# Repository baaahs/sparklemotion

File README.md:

# Sparkle Motion

Sparkle Motion[^1] is the system used to control the lights on [BAAAHS](http://baaahs.org), but it's
designed so it could be applied to pretty much any lighting project. It includes a browser-based
light show designer and performance interface, 3D light mapping, IP-based control protocol, and
custom LED control hardware and firmware. We designed it all pretty much from scratch, because
we're nerds. We hope you'll have some fun with it and maybe find it useful.
[^1]: It's a [Donnie Darko](https://www.youtube.com/watch?v=4QJCn04dfek) [reference](https://wakeupdonnie.fandom.com/wiki/Sparkle_Motion).

|  |  |
| --- | --- |
| The Sparkle Motion [Simulator](https://baaahs.github.io/sparklemotion) | BAAAHS at Black Rock City, 2019 |

**tl;dr:**

Shows are built out of small scripts called shaders, which are written in
[GLSL](https://www.khronos.org/opengl/wiki/Core_Language_(GLSL)). Lots of [awesome](http://glslsandbox.com/)
[free](https://www.shadertoy.com/) shaders and [dev](https://github.com/radixzz/awesome-glsl)
[tools](https://shaderfrog.com/) already exist on the internet. In the show designer, you can create or
import shaders, and attach them to buttons or sliders in a customizable performance UI. Shaders can be
combined in interesting ways to create new effects. You can make shows reactive to the environment by
connecting external sensor data—like a beat detector, midi controller, sound spectral analysis, or a
webcam—to shader variables.

Sparkle Motion can control LED strips using industry-standard
[sACN](https://artisticlicenceintegration.com/technology-brief/technology-resource/sacn-and-art-net/)
(or with our custom IP protocol), and Sharpy-style moving heads
over DMX, but it could be extended to control pretty much any kind of device. Lights can be mapped to a
3D model using computer vision. Individual lighting fixtures, or groups of fixtures, can be controlled
separately. All types of lights are controlled using the same language and idioms.

On the hardware side, Sparkle Motion includes specs for an ESP32-based controller which you could build
(or [buy from us](mailto:info@baaahs.org)!) managing WS2812-family LEDs, which is controlled over
Ethernet or WiFi.

----

## Show Designer

A _show_ is a collection of shaders, attached to UI elements, which can be arbitrarily combined and made reactive to the
environment using sensors,

(more TK)

## Scene Configuration

Sparkle Motion shows may be designed with a specific model and display fixtures in mind, but most shows can be applied to any model and fixtures.

To facilitate this, Sparkle Motion separates configuration of scene elements (the physical model and fixtures) from visuals and the performance interface.

| Term | Definition |
| --- | --- |
| **Driver** | A pluggable software component that can talk to specific types of display controller hardware, e.g. Brains, WLED, or DMX USB dongles. |
| **Controller** | A physical component directly connected to display hardware, e.g. a Sparkle Motion Brain, a WLED controller, or a DMX USB dongle. One or more fixtures may be associated with a controller. |
| **Fixture** | A physical display device, e.g. a moving head, a pixel array surface (a.k.a. panel), an LED bar, etc. |
| **Scene/Stage?** | The collection of fixtures under control of Sparkle Motion, which may be identified as model entities, or anonymous. |
| **Geometry** | The physical shape of a pixel array fixture. |
| **Model** | A 3-dimensional model to which fixtures may be mapped. Models may be composed of OBJ files and explicitly placed entities. |
| **Entity** | An object within the model, e.g. a sheep panel or eye. |

Note that in some cases a single controller may control multiple fixtures. Commonly, a physical DMX USB dongle may have
multiple moving heads attached. It's possible (but less common) for a single brain or WLED controller to be attached to
multiple physical lighting fixtures.

Also, it's possible for a DMX controller to manage multiple DMX universes, e.g. in the case of a WLED controller
managing more than 170 pixels.

ERD:

Driver <->* Controller <->* Fixture <->? Entity *<--> Model

A fixture may be *identified* or *anomnymous*.

Identified fixtures are associated with an entity in the model, and therefore have a known position and geometry.

Anonymous fixtures are mostly for stuff like bikers-by. They are randomly placed within the model. Pixel arrays are assumed to be linear.

## Mapper

Sparkle Motion's mapper lets you detect arbitrarily-placed lights on a 2D or 3D model using just a camera
connected to a laptop.

(more TK)

## Hardware

(more TK)

[More here](brain/sw/README.md).

## Simulator

The entire system can be run within a web browser in simulation mode ([here!](https://baaahs.github.io/sparklemotion)). Every component is modeled in software
so you can see how it will behave in the real world.

-->

## Very Old Documentation
* [Show API](show_api.md) (outdated)
* [API docs](https://baaahs.github.io/sparklemotion/doc/sparklemotion/) (outdated)

## Prerequisites

1. Install [Java](https://www.oracle.com/java/technologies/javase-jdk11-downloads.html)
    - If using an arm64 mac, DMX device support for the native build of sparklemotion requires an x86 jdk which can be
      downloaded [here](https://jdk.java.net/archive/).
    - Make sure to pick a JDK < version 20 as [gradle does not currently
      support
it](https://youtrack.jetbrains.com/issue/KT-57669/Add-Java-20-to-JvmTarget).
1. Open as a gradle project with [IntelliJ](https://www.jetbrains.com/idea/download/)

## Running from source

### Simulator Mode

In simulator mode, most of Sparkle Motion runs within a web browser.

Run this in a shell window; a browser window will open with the simulator:

    ./gradlew --continuous jsBrowserDevelopmentRun

### Production Mode

In production mode, Sparkle Motion runs in a JVM process and talks to real hardware.

To start it, run:

    ./gradlew run

If you don't have a Brain running locally, do this too:

    ./gradlew runBrainJvm
    
When running in this mode you should be able to access the UI at http://localhost:8004 

### Builds the production (minified) js package

To build the production minified js package run:

```
./gradlew jsBrowserWebpack
```

## CI & Deployment

Continuous build here: https://circleci.com/gh/baaahs/sparklemotion

Passing builds are automatically deployed here: https://baaahs.github.io/sparklemotion

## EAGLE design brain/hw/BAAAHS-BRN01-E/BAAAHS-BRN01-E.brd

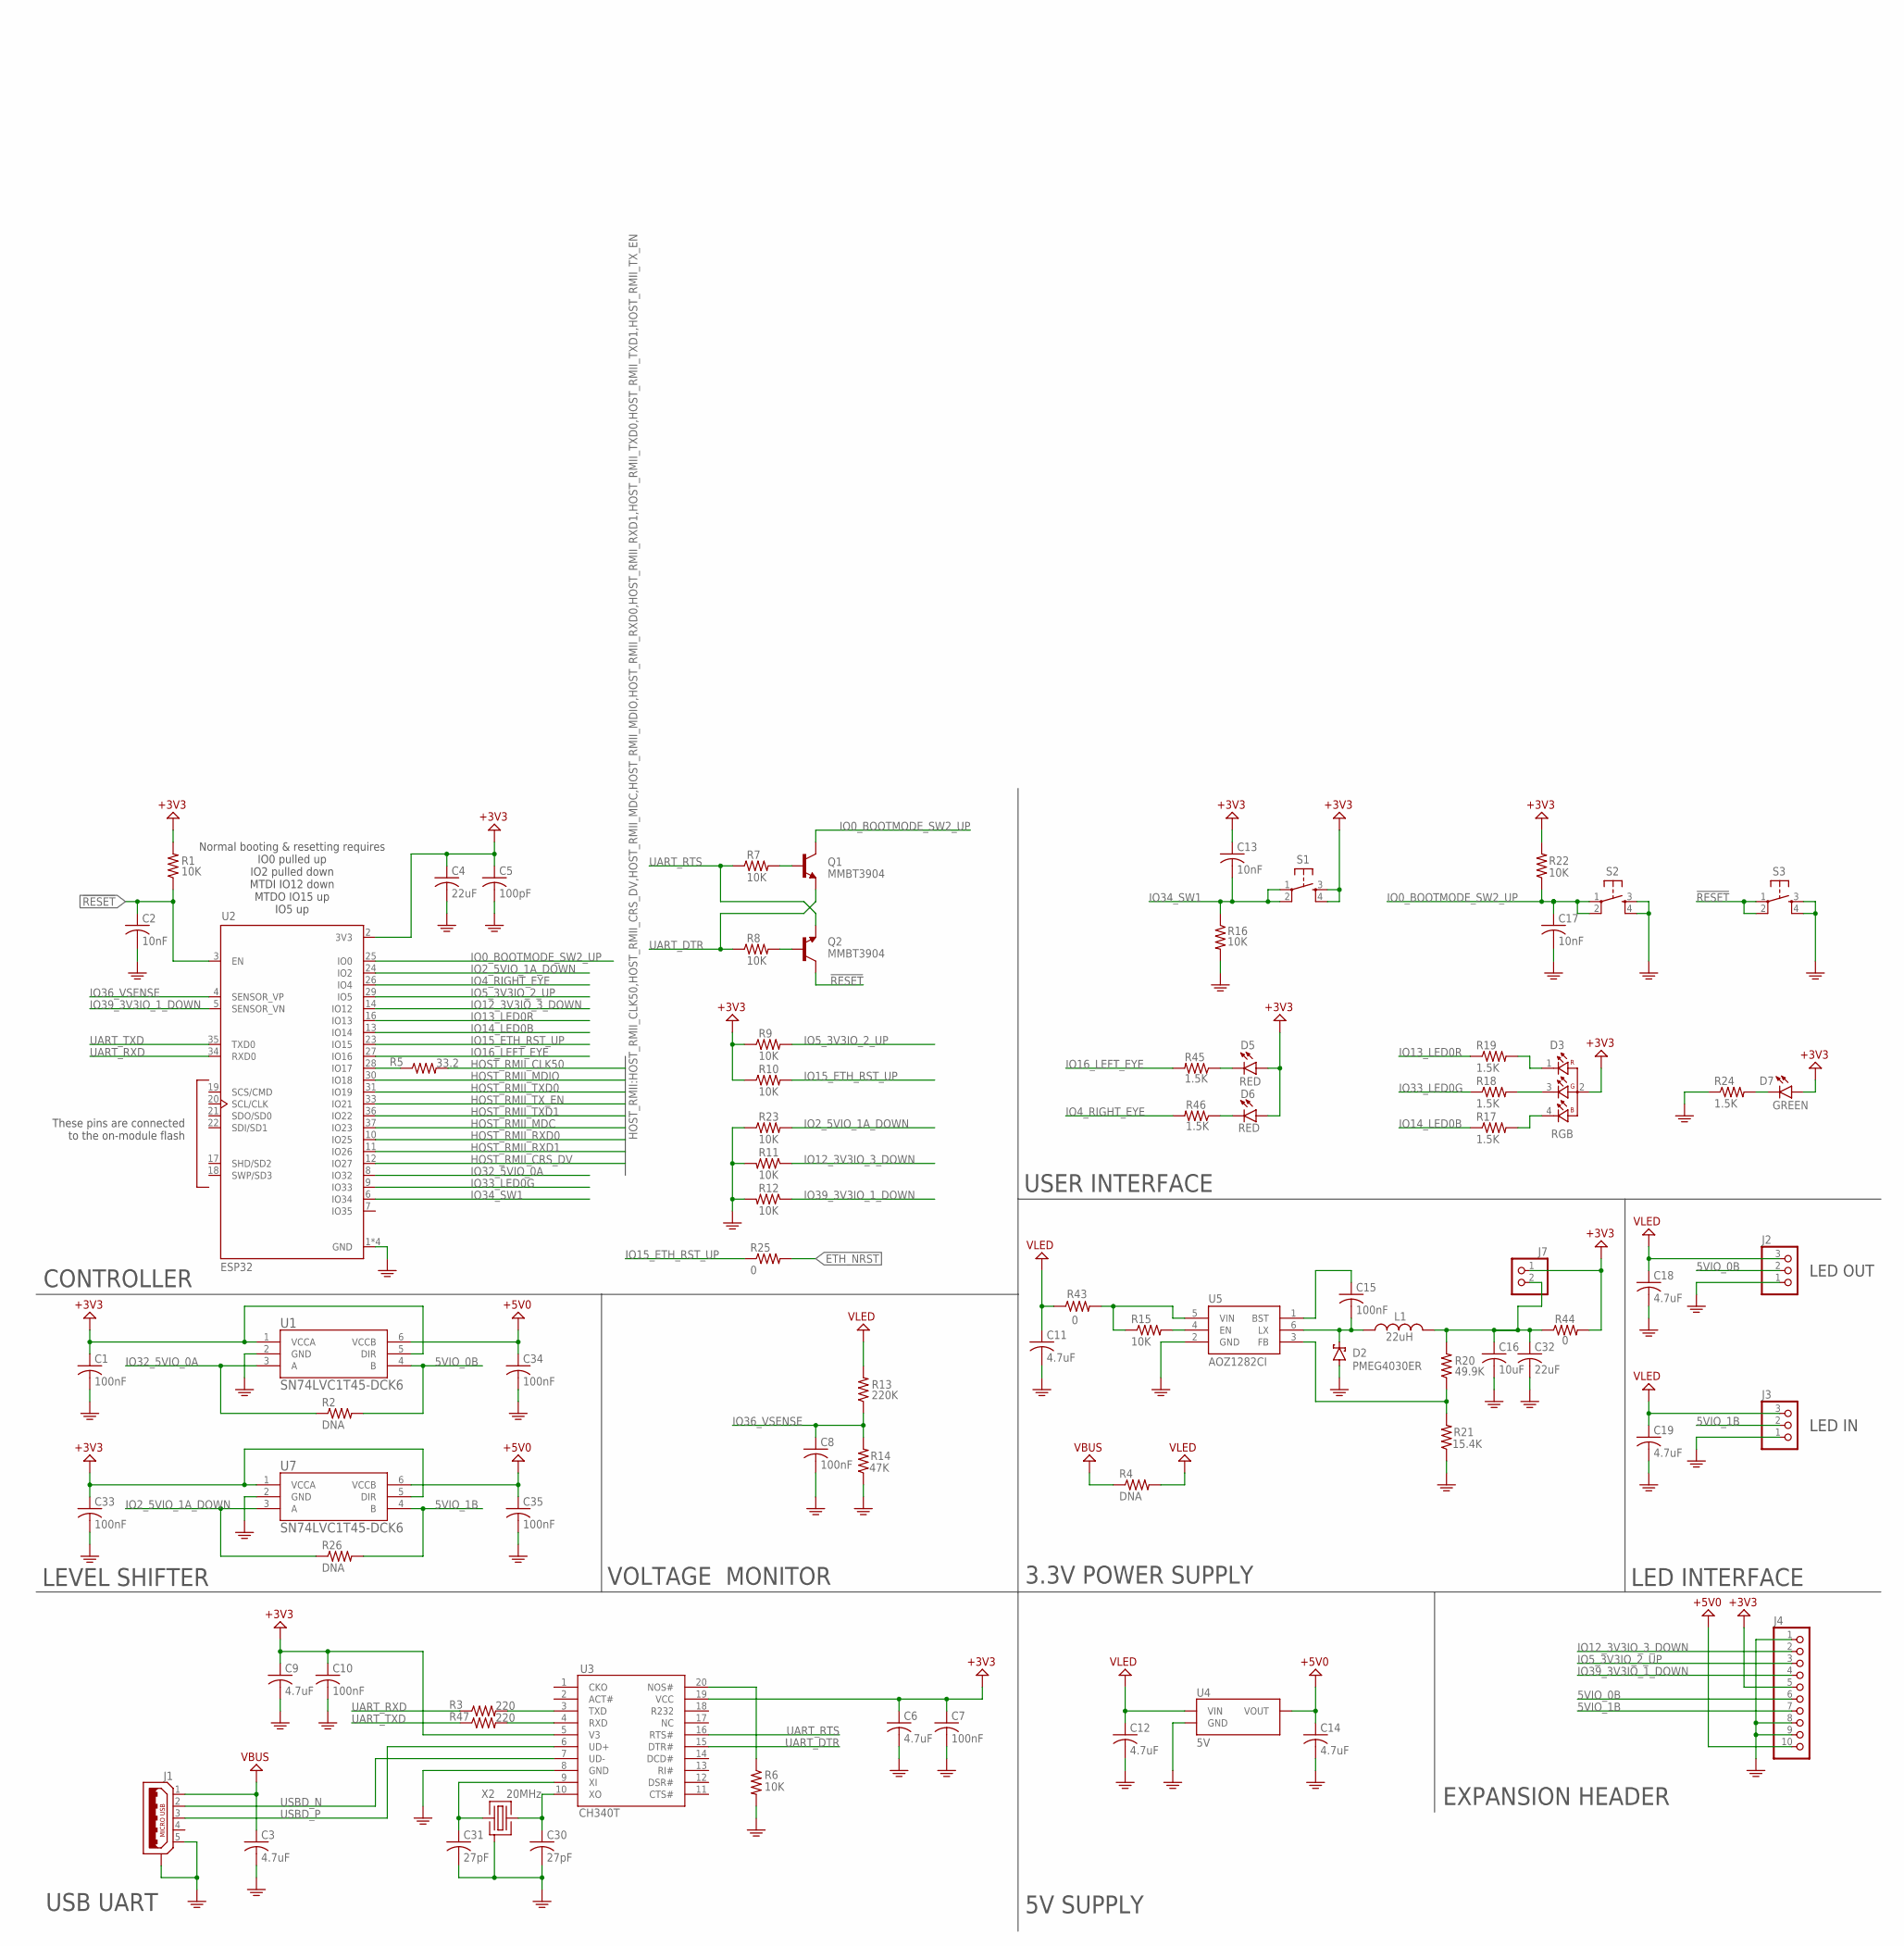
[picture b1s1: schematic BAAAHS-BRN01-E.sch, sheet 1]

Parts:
C1, C7, C8, C10, C15, C33, C34, C35: 100nF; C0402
C2, C13, C17: 10nF; C0402
C3, C6, C9, C14: 4.7uF; C0402
C4, C32: 22uF; C0603
C5: 100pF; C0402
C11, C12, C18, C19: 4.7uF; C0603
C16: 10uF; C0603
C30, C31: 27pF; C0402
D2: PMEG4030ER; SOD123
D3: RGB; RGB1616
D5, D6: RED; D0603
D7: GREEN; D0603
J1: USB_MICRO-FCI-USB_MICRO_A_RA; USB_MICRO_A_RA
J2, J3: PINHD1X3-20AWG; 3WAY_LED_WIRES
J4: PINHD1X10-1X10; 1X10
J7: PINHD1X2-1X02; 1X02
L1: 22uH; NRG4026
Q1, Q2: MMBT3904; SOT23
R1, R6, R7, R8, R9, R10, R11, R12, R15, R16, R22, R23: 10K; R0402
R2, R26: DNA; R0402
R3, R47: 220; R0402
R4: DNA; R0603
R5: 33.2; R0402
R13: 220K; R0402
R14: 47K; R0402
R17, R18, R19, R24, R45, R46: 1.5K; R0402
R20: 49.9K; R0402
R21: 15.4K; R0402
R25: 0; R0402
R43, R44: 0; R0603
S1, S2, S3: SW4-SM6MM; SM6MM
U1, U7: SN74LVC1T45-DCK6; DCK6
U2: ESP32; MODULE_ESP32WROOM32D
U3: CH340T; SSOP20
U4: 5V; SOT23
U5: AOZ1282CI; SOT23_6
X2: 20MHz; 3.2X2.5_4P

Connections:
3V3: C1.1, C4.1, C5.1, C6.1, C7.1, C9.1, C10.1, C13.1, C33.1, D3.2 (CA), D5.A, D6.A, D7.A, J4.5, J7.1, R1.2, R9.1, R10.1, R22.2, R44.2, S1.3 (S), S1.4 (S1), U1.1 (VCCA), U1.5 (DIR), U2.2 (3V3), U3.5 (V3), U3.19 (VCC), U7.1 (VCCA), U7.5 (DIR); also elsewhere on the board
5V0: C14.1, C34.1, C35.1, J4.10, U1.6 (VCCB), U4.2 (VOUT), U7.6 (VCCB)
5VIO_0B: J2.2, J4.6, R2.2, U1.4 (B)
5VIO_1B: J3.2, J4.7, R26.2, U7.4 (B)
!RESET: C2.1, Q2.3 (C), R1.1, S3.1, S3.2 (P1), U2.3 (EN)
ETH_NRST: R25.2; also elsewhere on the board
FB: R20.1, R21.2, U5.3 (FB)
GND: C1.2, C2.2, C3.2, C4.2, C5.2, C6.2, C7.2, C8.2, C9.2, C10.2, C11.2, C12.2, C14.2, C16.2, C17.2, C18.2, C19.2, C30.2, C31.2, C32.2, C33.2, C34.2, C35.2, D2.A, J1.5, J1.S1, J1.S2 (S1), J1.S3 (S1), J1.S4 (S1), J1.S5 (S1), J1.S6 (S1), J2.1 (3), J3.1 (3), J4.1, J4.8, J4.9, R6.2, R11.2, R12.2, R14.1, R16.2, R21.1, R23.1, R24.1, S2.3 (S), S2.4 (S1), S3.3 (S), S3.4 (S1), U1.2 (GND), U2.1 (GND), U2.15 (GND), U2.38 (GND), U2.39 (GND), U3.8 (GND), U4.1 (GND), U5.2 (GND), U7.2 (GND), X2.2 (SH), X2.4 (SH); also elsewhere on the board
HOST_RMII_CLK50: R5.2; also elsewhere on the board
HOST_RMII_CRS_DV: U2.12 (IO27); also elsewhere on the board
HOST_RMII_MDC: U2.37 (IO23); also elsewhere on the board
HOST_RMII_MDIO: U2.30 (IO18); also elsewhere on the board
HOST_RMII_RXD0: U2.10 (IO25); also elsewhere on the board
HOST_RMII_RXD1: U2.11 (IO26); also elsewhere on the board
HOST_RMII_TXD0: U2.31 (IO19); also elsewhere on the board
HOST_RMII_TXD1: U2.36 (IO22); also elsewhere on the board
HOST_RMII_TX_EN: U2.33 (IO21); also elsewhere on the board
IO0_BOOTMODE_SW2_UP: C17.1, Q1.3 (C), R22.1, S2.1, S2.2 (P1), U2.25 (IO0)
IO2_5VIO_1A_DOWN: R23.2, R26.1, U2.24 (IO2), U7.3 (A)
IO4_RIGHT_EYE: R46.2, U2.26 (IO4)
IO5_3V3IO_2_UP: J4.3, R9.2, U2.29 (IO5)
IO12_3V3IO_3_DOWN: J4.2, R11.1, U2.14 (IO12)
IO13_LED0R: R19.1, U2.16 (IO13)
IO14_LED0B: R17.1, U2.13 (IO14)
IO15_ETH_RST_UP: R10.2, R25.1, U2.23 (IO15)
IO16_LEFT_EYE: R45.2, U2.27 (IO16)
IO32_5VIO_0A: R2.1, U1.3 (A), U2.8 (IO32)
IO33_LED0G: R18.1, U2.9 (IO33)
IO34_SW1: C13.2, R16.1, S1.1, S1.2 (P1), U2.6 (IO34)
IO36_VSENSE: C8.1, R13.1, R14.2, U2.4 (SENSOR_VP)
IO39_3V3IO_1_DOWN: J4.4, R12.1, U2.5 (SENSOR_VN)
unnamed: R5.1, U2.28 (IO17)
unnamed: R15.2, U5.4 (EN)
unnamed: C15.2, D2.C, L1.1, U5.6 (LX)
unnamed: R3.2, U3.3 (TXD)
unnamed: R47.2, U3.4 (RXD)
unnamed: Q2.1 (B), R8.2
unnamed: Q1.1 (B), R7.2
unnamed: D3.4 (B), R17.2
unnamed: D3.3 (G), R18.2
unnamed: D3.1 (R), R19.2
unnamed: C31.1, U3.9 (XI), X2.3 (2)
unnamed: C30.1, U3.10 (XO), X2.1
unnamed: D7.C, R24.2
unnamed: C15.1, U5.1 (BST)
unnamed: R15.1, R43.2, U5.5 (VIN)
unnamed: C16.1, C32.1, J7.2, L1.2, R20.2, R44.1
unnamed: D6.C, R46.1
unnamed: D5.C, R45.1
NOS#: R6.1, U3.20 (NOS#)
UART_DTR: Q1.2 (E), R8.1, U3.15 (DTR#)
UART_RTS: Q2.2 (E), R7.1, U3.16 (RTS#)
UART_RXD: R3.1, U2.34 (RXD0)
UART_TXD: R47.1, U2.35 (TXD0)
USBD_N: J1.2, U3.7 (UD-)
USBD_P: J1.3, U3.6 (UD+)
VBUS: C3.1, J1.1, R4.1
VLED: C11.1, C12.1, C18.1, C19.1, J2.3 (1), J3.3 (1), R4.2, R13.2, R43.1, U4.3 (VIN)

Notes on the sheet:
Normal booting & resetting requires IO0 pulled up IO2 pulled down MTDI IO12 down MTDO IO15 up IO5 up
These pins are connected to the on-module flash
CONTROLLER
LEVEL SHIFTER
USB UART
5V SUPPLY
3.3V POWER SUPPLY
EXPANSION HEADER
LED INTERFACE
USER INTERFACE
VOLTAGE MONITOR
LED OUT
LED IN

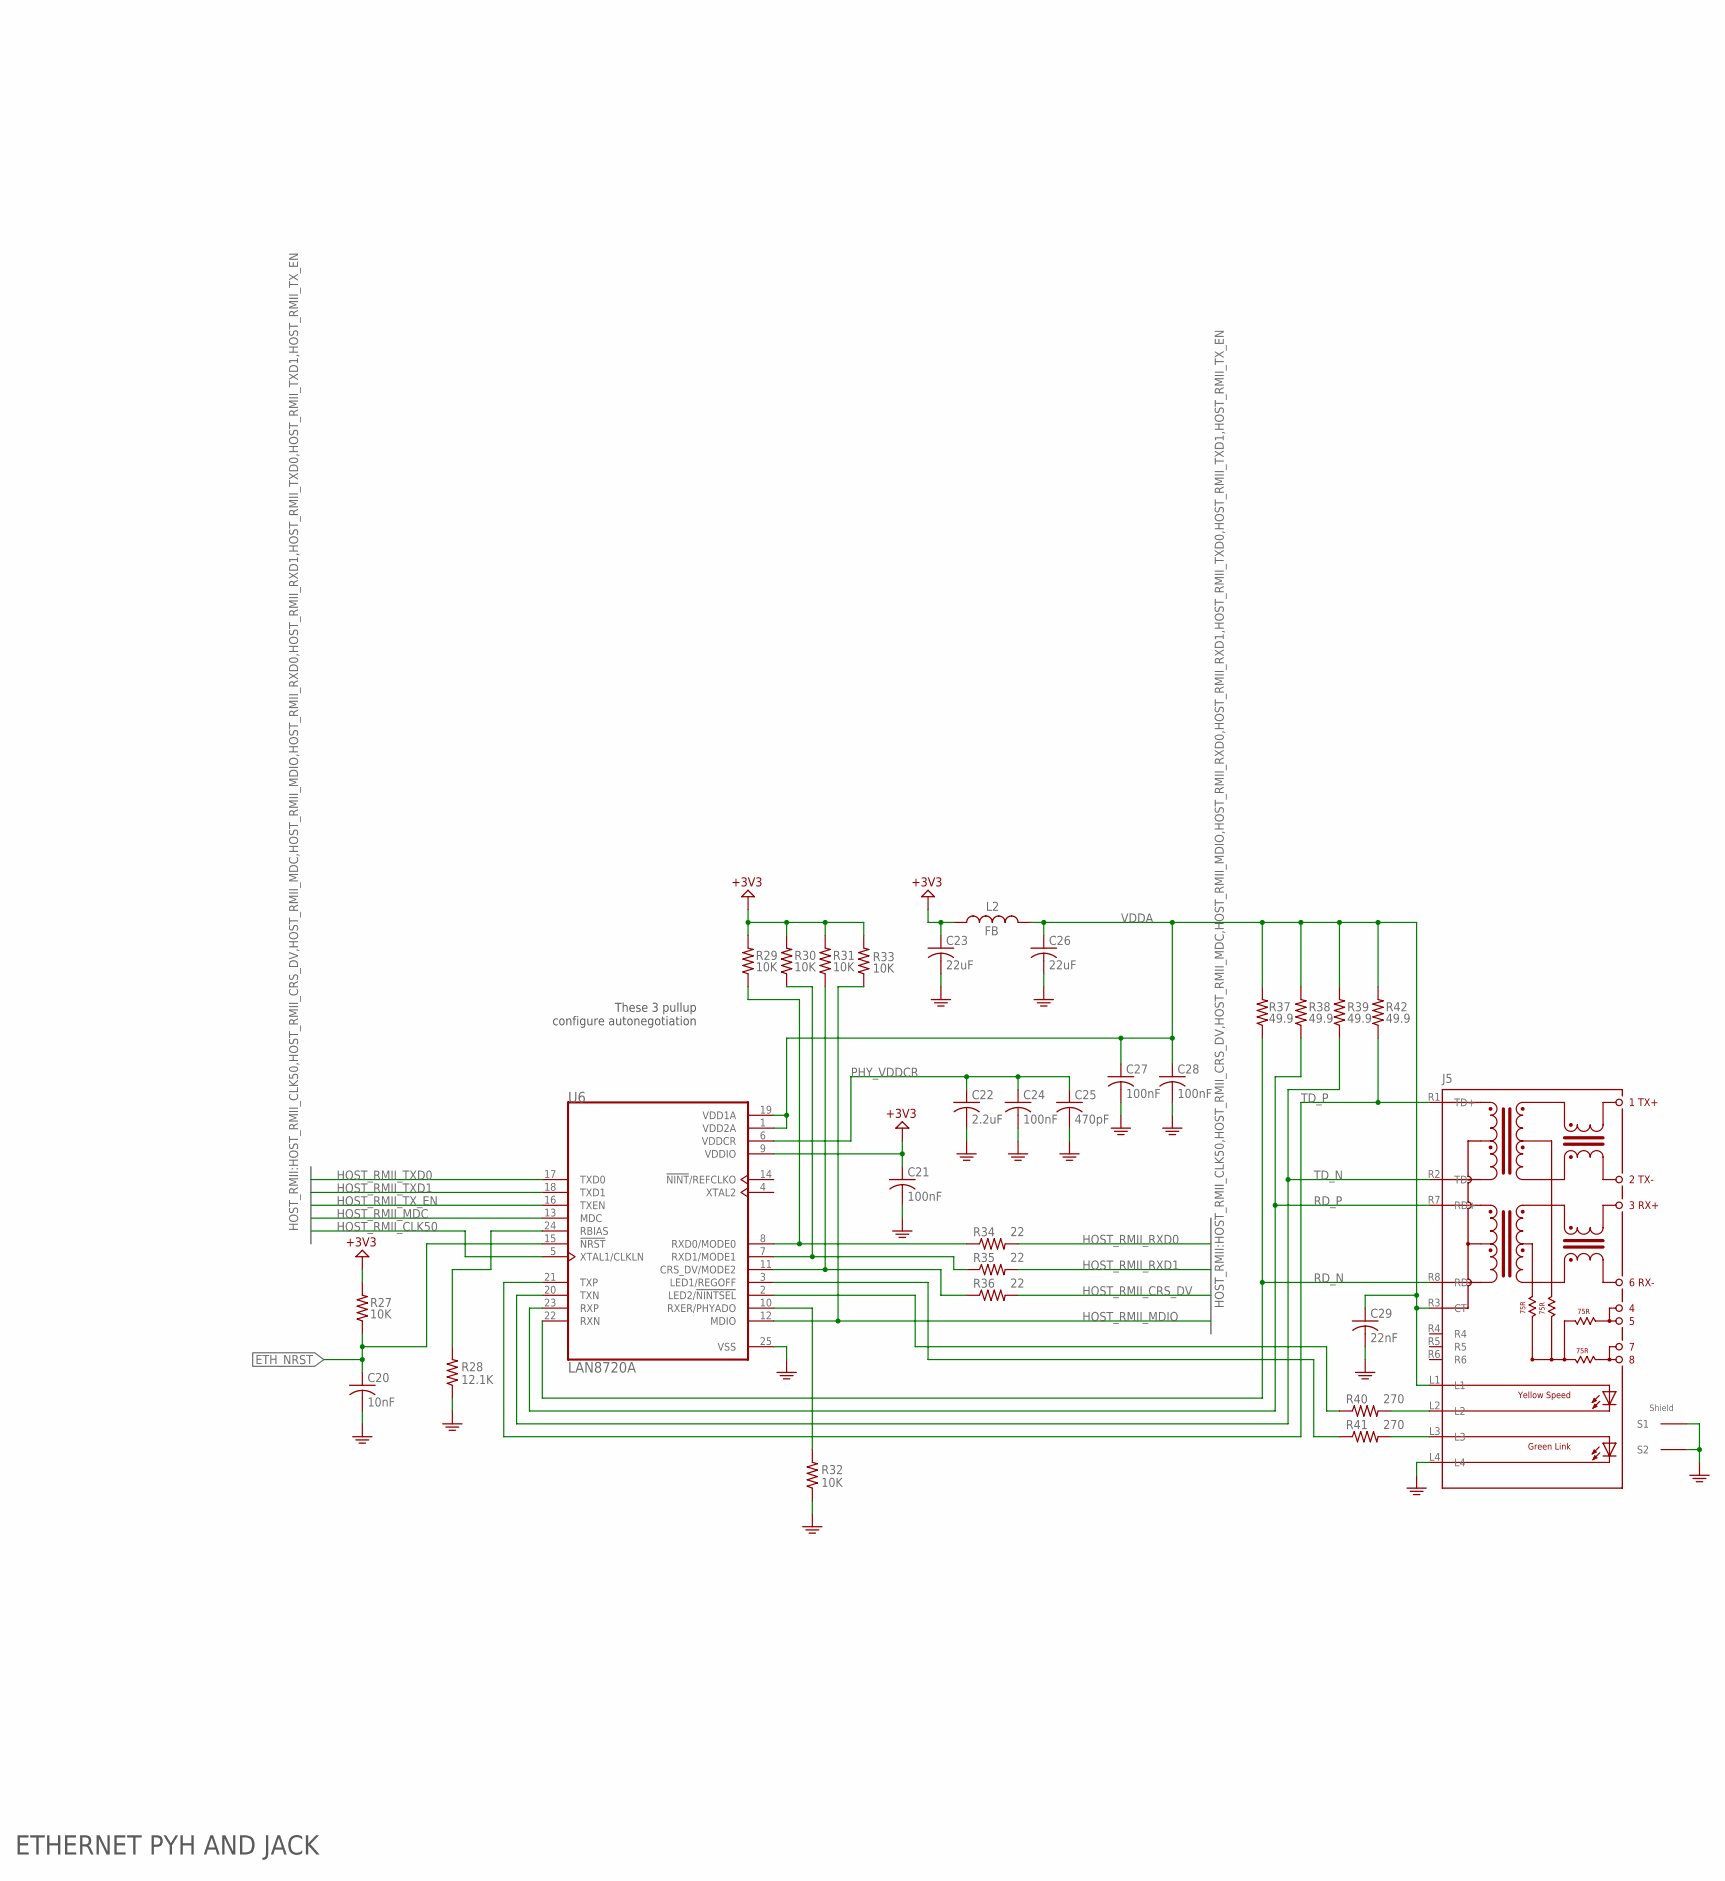
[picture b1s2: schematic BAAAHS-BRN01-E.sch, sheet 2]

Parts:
C20: 10nF; C0402
C21, C24, C27, C28: 100nF; C0402
C22: 2.2uF; C0603
C23, C26: 22uF; C0603
C25: 470pF; C0402
C29: 22nF; C0402
J5: RB1-125BAG1A; WIZNET_RB1-125BAG1A
L2: FB; L0603
R27, R29, R30, R31, R32, R33: 10K; R0402
R28: 12.1K; R0402
R34, R35, R36: 22; R0402
R37, R38, R39, R42: 49.9; R0402
R40, R41: 270; R0402
U6: LAN8720A; QFN50P400X400X100-25N

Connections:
3V3: C21.1, C23.1, L2.1, R27.2, R29.2, R30.2, R31.2, R33.2, U6.9 (VDDIO); also elsewhere on the board
ETH_NRST: C20.1, R27.1, U6.15 (!NRST); also elsewhere on the board
GND: C20.2, C21.2, C22.2, C23.2, C24.2, C25.2, C26.2, C27.2, C28.2, C29.2, J5.L4, J5.S1, J5.S2, R28.1, R32.1, U6.25 (VSS); also elsewhere on the board
HOST_RMII_CLK50: U6.5 (XTAL1/CLKLN); also elsewhere on the board
HOST_RMII_CRS_DV: R36.2; also elsewhere on the board
HOST_RMII_MDC: U6.13 (MDC); also elsewhere on the board
HOST_RMII_MDIO: R33.1, U6.12 (MDIO); also elsewhere on the board
HOST_RMII_RXD0: R34.2; also elsewhere on the board
HOST_RMII_RXD1: R35.2; also elsewhere on the board
HOST_RMII_TXD0: U6.17 (TXD0); also elsewhere on the board
HOST_RMII_TXD1: U6.18 (TXD1); also elsewhere on the board
HOST_RMII_TX_EN: U6.16 (TXEN); also elsewhere on the board
unnamed: J5.L3, R41.2
unnamed: R31.1, R36.1, U6.11 (CRS_DV/MODE2)
unnamed: R30.1, R35.1, U6.7 (RXD1/MODE1)
unnamed: R29.1, R34.1, U6.8 (RXD0/MODE0)
unnamed: R28.2, U6.24 (RBIAS)
unnamed: R41.1, U6.3 (LED1/REGOFF)
unnamed: R40.1, U6.2 (LED2/!NINTSEL!)
unnamed: J5.L2, R40.2
unnamed: R32.2, U6.10 (RXER/PHYADO)
PHY_VDDCR: C22.1, C24.1, C25.1, U6.6 (VDDCR)
RD_N: J5.R8 (RD-), R37.1, U6.22 (RXN)
RD_P: J5.R7 (RD+), R38.1, U6.23 (RXP)
TD_N: J5.R2 (TD-), R39.1, U6.20 (TXN)
TD_P: J5.R1 (TD+), R42.1, U6.21 (TXP)
VDDA: C26.1, C27.1, C28.1, C29.1, J5.L1, J5.R3 (CT), L2.2, R37.2, R38.2, R39.2, R42.2, U6.1 (VDD2A), U6.19 (VDD1A)

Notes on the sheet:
These 3 pullup configure autonegotiation
ETHERNET PYH AND JACK

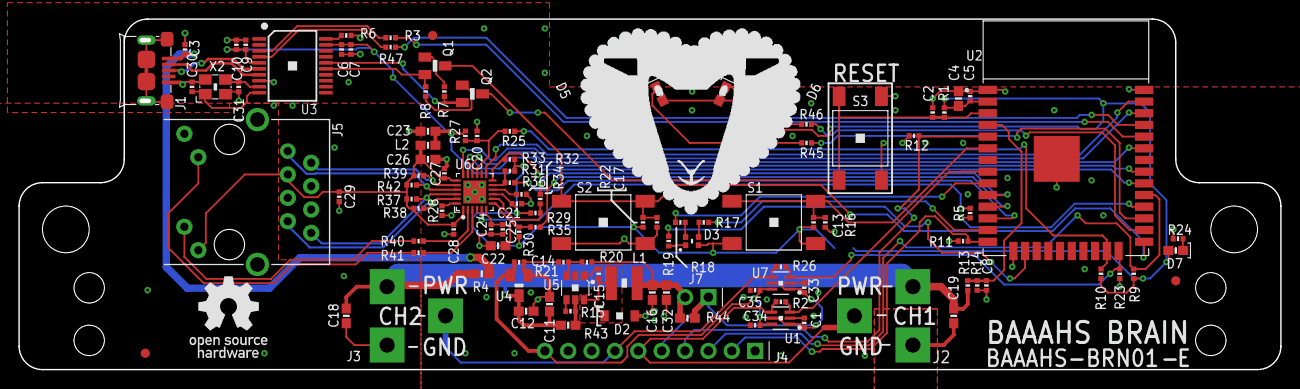
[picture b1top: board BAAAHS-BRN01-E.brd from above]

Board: 4 copper layers, 136.8 x 37.7 mm, 117 parts (1 on the bottom side), 73 nets.

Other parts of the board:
F1, F2, F3: FIDUCIAL_1MM
U$1: NOTE_ENIG_BLACK_NARROW
U$9: BAAAHS_FABRICATION_TITLEBLOCK
U$10: STACKUP_4LAYER_1.6MM
U$16: BAAAHS_TOP_ASSEMBLY_TITLEBLOCK
U$17: OPEN_HARDWARE_LOGO_350
U$18: BAAAHS_LOGO

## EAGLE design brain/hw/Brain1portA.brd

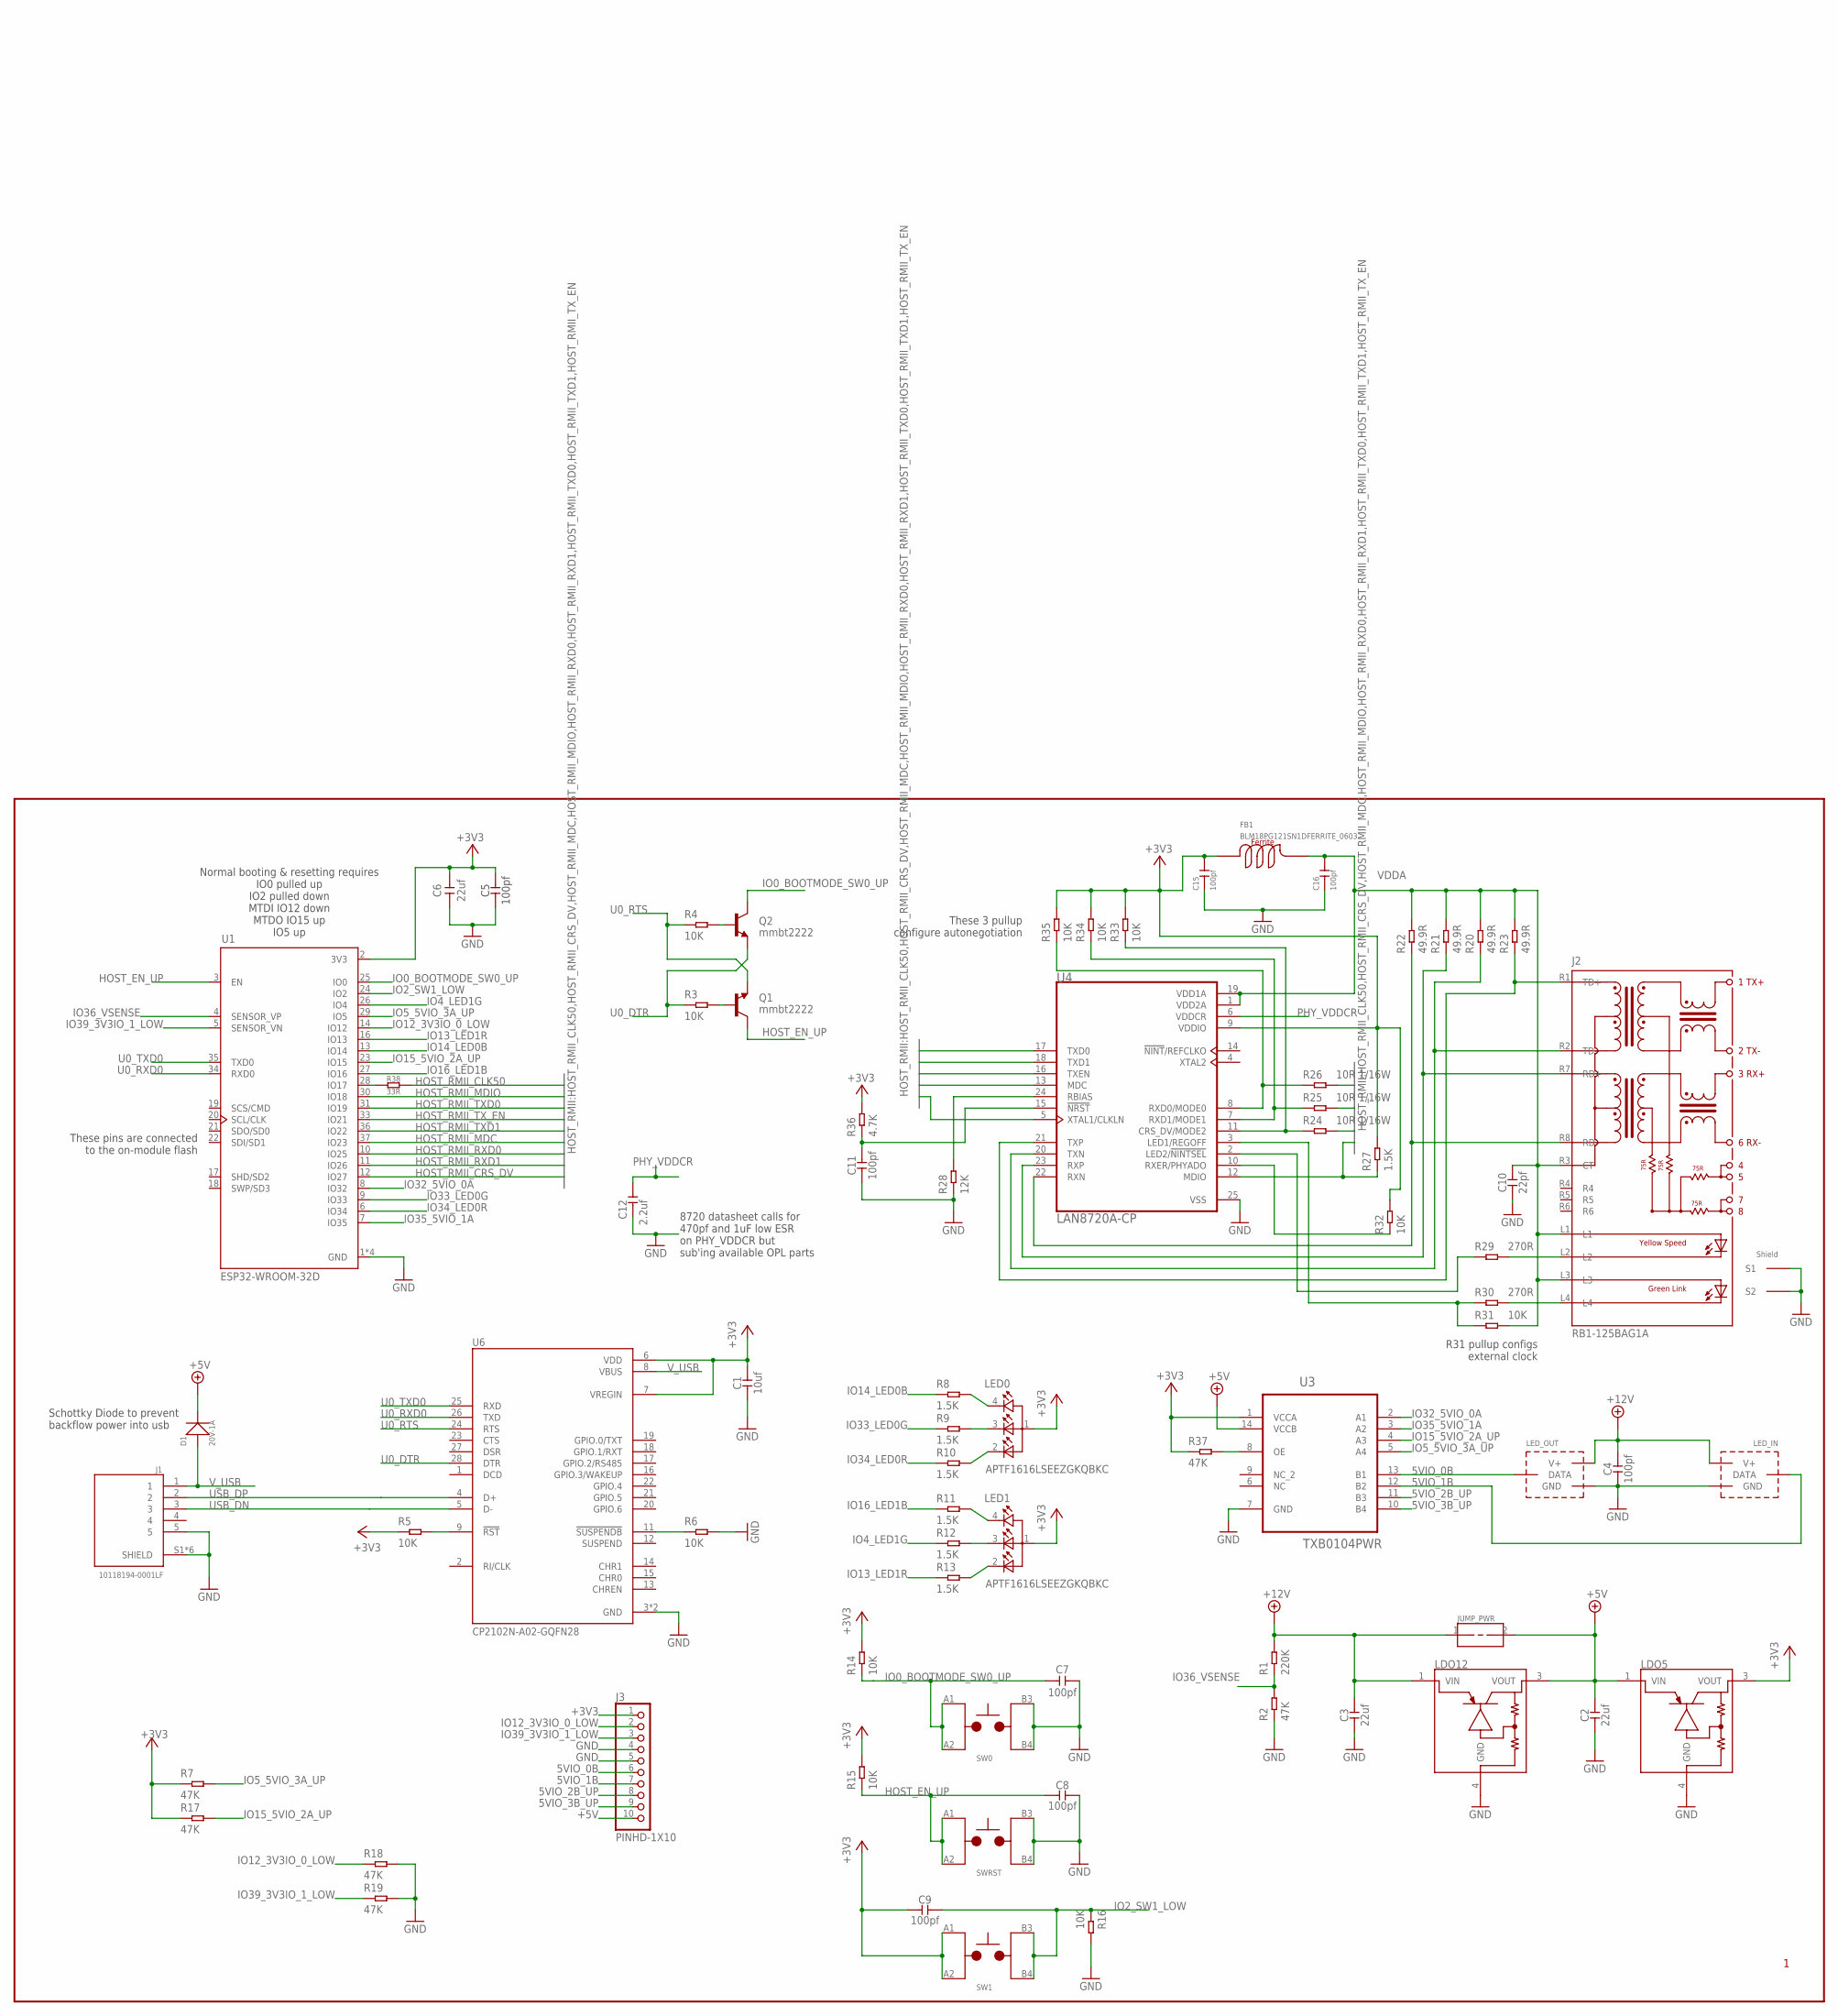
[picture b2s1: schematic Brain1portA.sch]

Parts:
C1: 10uf; C0402
C2, C3, C6: 22uf; C0805
C4, C5, C7, C8, C9, C11, C15, C16: 100pf; C0402
C10: 22pf; C0402
C12: 2.2uf; C0603
D1: 20V-1A; SOD-123
FB1: BLM18PG121SN1DFERRITE_0603; L0603
J1: 10118194-0001LF; AMPHENOL_10118194-0001LF
J2: RB1-125BAG1A; WIZNET_RB1-125BAG1A
J3: PINHD-1X10; 1X10-BIG
JUMP_PWR: PWR_SUPPLY_SHORT050_DRILLED; SHORT_050_DRILLED
LDO5, LDO12: NCP5501DPAK3; TO229P990X238-3
LED0, LED1: APTF1616LSEEZGKQBKC; LEDSC160X160X070-4N
LED_IN: 3WAY_LED_CONWIRES; 3WAY_LED_WIRES
LED_OUT: 3WAY_LED_CONWIRES; 3WAY_LED_WIRES
Q1, Q2: mmbt2222; SOT23-BEC
R1: 220K; R0402
R2, R7, R17, R18, R19, R37: 47K; R0402
R3, R4, R5, R6, R14, R15, R16, R31, R32, R33, R34, R35: 10K; R0402
R8, R9, R10, R11, R12, R13, R27: 1.5K; R0402
R20, R21, R22, R23: 49.9R; R0402
R24, R25, R26: 10R 1/16W; R0402
R28: 12K; R0402
R29, R30: 270R; R0402
R36: 4.7K; R0402
R38: 33R; R0603
SW0, SW1: TL3301T3301SWITCH; SW-4
SWRST: TL3301T3301SWITCH; SW-4
U1: ESP32-WROOM-32D; MODULE_ESP32-WROOM-32D
U3: TXB0104PWR; SOP65P640X120-14N
U4: LAN8720A-CP; QFN50P400X400X100-25N
U6: CP2102N-A02-GQFN28; QFN50P500X500X80-29N

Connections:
5VIO_0B: J3.6, LED_OUT.DATA, U3.13 (B1)
5VIO_1B: J3.7, LED_IN.DATA, U3.12 (B2)
5VIO_2B_UP: J3.8, U3.11 (B3)
5VIO_3B_UP: J3.9, U3.10 (B4)
+3V3: C1.1, C5.1, C6.1, C9.1, C15.2, FB1.1, J3.1, LDO5.3 (VOUT), LED0.1, LED1.1, R5.1, R7.1, R14.2, R15.2, R17.1, R27.2, R32.2, R33.2, R34.2, R35.2, R36.2, R37.1, SW1.A1 (1), SW1.A2 (2), U1.2 (3V3), U3.1 (VCCA), U4.9 (VDDIO), U6.6 (VDD), U6.7 (VREGIN)
+5V: C2.1, D1.-, J3.10, JUMP_PWR.2, LDO5.1 (VIN), LDO12.3 (VOUT), U3.14 (VCCB)
+12V: C3.1, C4.1, JUMP_PWR.1, LDO12.1 (VIN), LED_IN.V+, LED_OUT.V+, R1.2
GND: C1.2, C2.2, C3.2, C4.2, C5.2, C6.2, C7.2, C8.2, C10.2, C11.2, C12.2, C15.1, C16.1, J1.5, J1.S1 (SHIELD), J1.S2 (SHIELD), J1.S3 (SHIELD), J1.S4 (SHIELD), J1.S5 (SHIELD), J1.S6 (SHIELD), J2.S1, J2.S2, J3.4, J3.5, LDO5.4 (GND), LDO12.4 (GND), LED_IN.GND, LED_OUT.GND, R2.1, R6.2, R16.2, R18.2, R19.2, R28.1, SW0.B3 (3), SW0.B4 (4), SWRST.B3 (3), SWRST.B4 (4), U1.1 (GND), U1.15 (GND), U1.38 (GND), U1.39 (GND), U3.7 (GND), U4.25 (VSS), U6.3 (GND), U6.29 (GND)
HOST_EN_UP: C8.1, Q1.C, R15.1, SWRST.A1 (1), SWRST.A2 (2), U1.3 (EN)
HOST_RMII_CLK50: R38.2, U4.5 (XTAL1/CLKLN)
HOST_RMII_CRS_DV: R24.2, U1.12 (IO27)
HOST_RMII_MDC: U1.37 (IO23), U4.13 (MDC)
HOST_RMII_MDIO: R27.1, U1.30 (IO18), U4.12 (MDIO)
HOST_RMII_RXD0: R26.2, U1.10 (IO25)
HOST_RMII_RXD1: R25.2, U1.11 (IO26)
HOST_RMII_TXD0: U1.31 (IO19), U4.17 (TXD0)
HOST_RMII_TXD1: U1.36 (IO22), U4.18 (TXD1)
HOST_RMII_TX_EN: U1.33 (IO21), U4.16 (TXEN)
IO0_BOOTMODE_SW0_UP: C7.1, Q2.C, R14.1, SW0.A1 (1), SW0.A2 (2), U1.25 (IO0)
IO2_SW1_LOW: C9.2, R16.1, SW1.B3 (3), SW1.B4 (4), U1.24 (IO2)
IO4_LED1G: R12.1, U1.26 (IO4)
IO5_5VIO_3A_UP: R7.2, U1.29 (IO5), U3.5 (A4)
IO12_3V3IO_0_LOW: J3.2, R18.1, U1.14 (IO12)
IO13_LED1R: R13.1, U1.16 (IO13)
IO14_LED0B: R8.1, U1.13 (IO14)
IO15_5VIO_2A_UP: R17.2, U1.23 (IO15), U3.4 (A3)
IO16_LED1B: R11.1, U1.27 (IO16)
IO32_5VIO_0A: U1.8 (IO32), U3.2 (A1)
IO33_LED0G: R9.1, U1.9 (IO33)
IO34_LED0R: R10.1, U1.6 (IO34)
IO35_5VIO_1A: U1.7 (IO35), U3.3 (A2)
IO36_VSENSE: R1.1, R2.2, U1.4 (SENSOR_VP)
IO39_3V3IO_1_LOW: J3.3, R19.1, U1.5 (SENSOR_VN)
unnamed: R38.1, U1.28 (IO17)
unnamed: R5.2, U6.9 (!RST)
unnamed: R6.1, U6.11 (!SUSPENDB)
unnamed: Q1.B, R3.2
unnamed: Q2.B, R4.2
unnamed: LED0.4, R8.2
unnamed: LED0.3, R9.2
unnamed: LED0.2, R10.2
unnamed: J2.R8 (RD-), R22.1, U4.22 (RXN)
unnamed: J2.R7 (RD+), R21.1, U4.23 (RXP)
unnamed: LED1.4, R11.2
unnamed: LED1.3, R12.2
unnamed: LED1.2, R13.2
unnamed: J2.R2 (TD-), R20.1, U4.20 (TXN)
unnamed: R24.1, R33.1, U4.11 (CRS_DV/MODE2)
unnamed: J2.R1 (TD+), R23.1, U4.21 (TXP)
unnamed: R25.1, R34.1, U4.7 (RXD1/MODE1)
unnamed: R26.1, R35.1, U4.8 (RXD0/MODE0)
unnamed: R28.2, U4.24 (RBIAS)
unnamed: R30.1, R31.1, U4.3 (LED1/REGOFF)
unnamed: R29.1, U4.2 (LED2/!NINTSEL!)
unnamed: J2.L2, R29.2
unnamed: J2.L4, R30.2
unnamed: R37.2, U3.8 (OE)
unnamed: C11.1, R36.1, U4.15 (!NRST)
unnamed: R32.1, U4.10 (RXER/PHYADO)
PHY_VDDCR: C12.1, U4.6 (VDDCR)
U0_DTR: Q2.E, R3.1, U6.28 (DTR)
U0_RTS: Q1.E, R4.1, U6.24 (RTS)
U0_RXD0: U1.34 (RXD0), U6.26 (TXD)
U0_TXD0: U1.35 (TXD0), U6.25 (RXD)
USB_DN: J1.3, U6.5 (D-)
USB_DP: J1.2, U6.4 (D+)
VDDA: C10.1, C16.2, FB1.2, J2.L1, J2.L3, J2.R3 (CT), R20.2, R21.2, R22.2, R23.2, R31.2, U4.1 (VDD2A), U4.19 (VDD1A)
V_USB: D1.+, J1.1, U6.8 (VBUS)

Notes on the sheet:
Schottky Diode to prevent backflow power into usb
Normal booting & resetting requires IO0 pulled up IO2 pulled down MTDI IO12 down MTDO IO15 up IO5 up
These pins are connected to the on-module flash
These 3 pullup configure autonegotiation
8720 datasheet calls for 470pf and 1uF low ESR on PHY_VDDCR but sub'ing available OPL parts
R31 pullup configs external clock

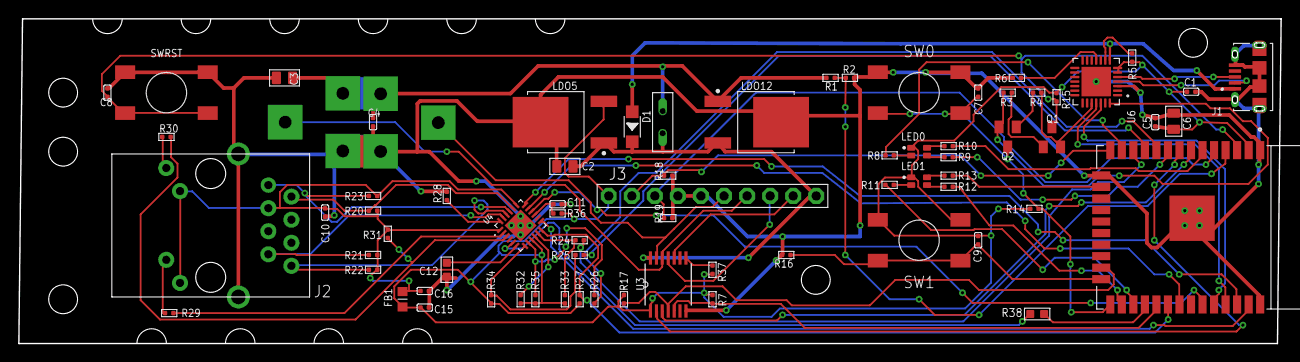
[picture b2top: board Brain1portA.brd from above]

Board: 2 copper layers, 139.0 x 35.8 mm, 73 parts (1 on the bottom side), 68 nets.
